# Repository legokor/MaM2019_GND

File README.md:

# MaM2019-GND

Lábkiosztás:

| ESP32 | LoRa  | Panel |
|-------|-------|-------|
| 5     | NSS   |       |
| 12    |       | Pin8  |
| 14    |       | Pin6  |
| 17    | RESET |       |
| 18    | SCK   |       |
| 19    | MISO  |       |
| 23    | MOSI  |       |
| 25    |       | Pin1  |
| 26    |       | Pin2  |
| 27    |       | Pin4  |
| 32    |       | Pin5  |
| 33    |       | Pin3  |
| 34    | DIO0  |       |
| 35    |       | Pin7  |

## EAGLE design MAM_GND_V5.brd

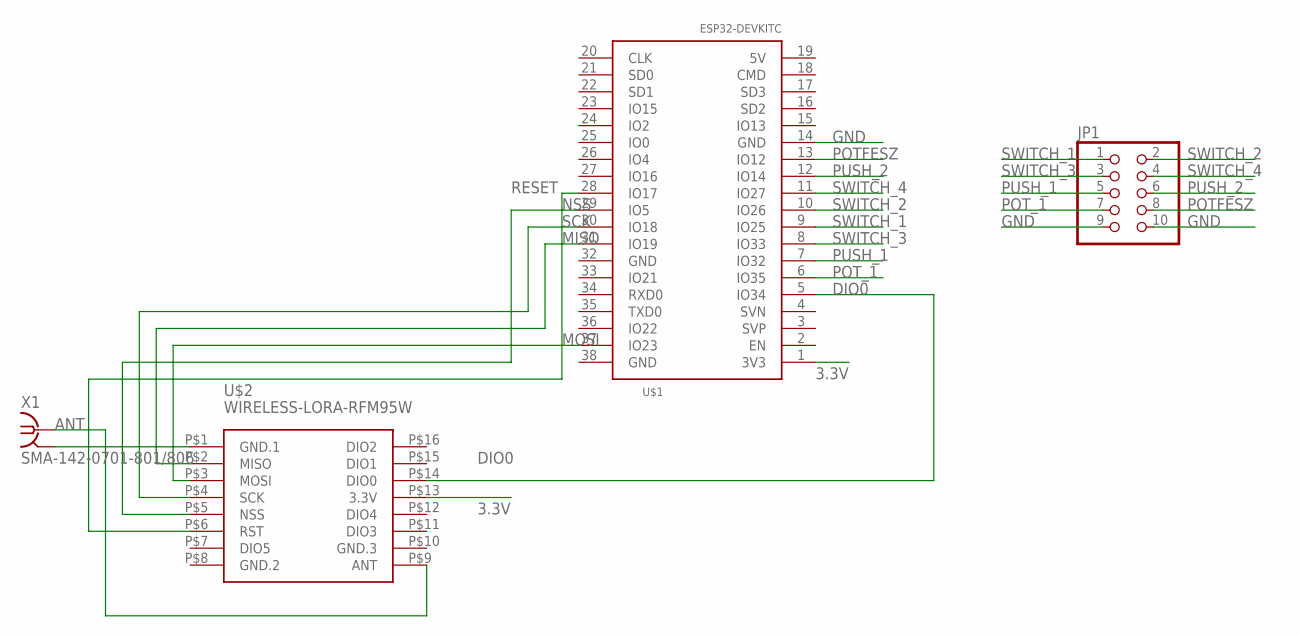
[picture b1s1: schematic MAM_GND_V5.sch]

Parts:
JP1: PINHD-2X5; 2X05
U$1: ESP32DEVKITC; ESP32-DEVKITC
U$2: WIRELESS-LORA-RFM95W; LORA-BREAKOUT
X1: SMA-142-0701-801/806; J502-ND-142-0701-801/806

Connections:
3.3V: U$1.1 (3V3), U$2.P$13 (3.3V)
ANT: U$2.P$9 (ANT), X1.1
DIO0: U$1.5 (IO34), U$2.P$14 (DIO0)
GND: JP1.9, JP1.10, U$1.14 (GND), U$2.P$1 (GND.1), X1.G@1 (2), X1.G@2 (2), X1.G@3 (2), X1.G@4 (2)
GND.2: U$2.P$8 (GND.2)
GND.3: U$2.P$10 (GND.3)
MISO: U$1.31 (IO19), U$2.P$2 (MISO)
MOSI: U$1.37 (IO23), U$2.P$3 (MOSI)
NSS: U$1.29 (IO5), U$2.P$5 (NSS)
POTFESZ: JP1.8, U$1.13 (IO12)
POT_1: JP1.7, U$1.6 (IO35)
PUSH_1: JP1.5, U$1.7 (IO32)
PUSH_2: JP1.6, U$1.12 (IO14)
RESET: U$1.28 (IO17), U$2.P$6 (RST)
SCK: U$1.30 (IO18), U$2.P$4 (SCK)
SWITCH_1: JP1.1, U$1.9 (IO25)
SWITCH_2: JP1.2, U$1.10 (IO26)
SWITCH_3: JP1.3, U$1.8 (IO33)
SWITCH_4: JP1.4, U$1.11 (IO27)

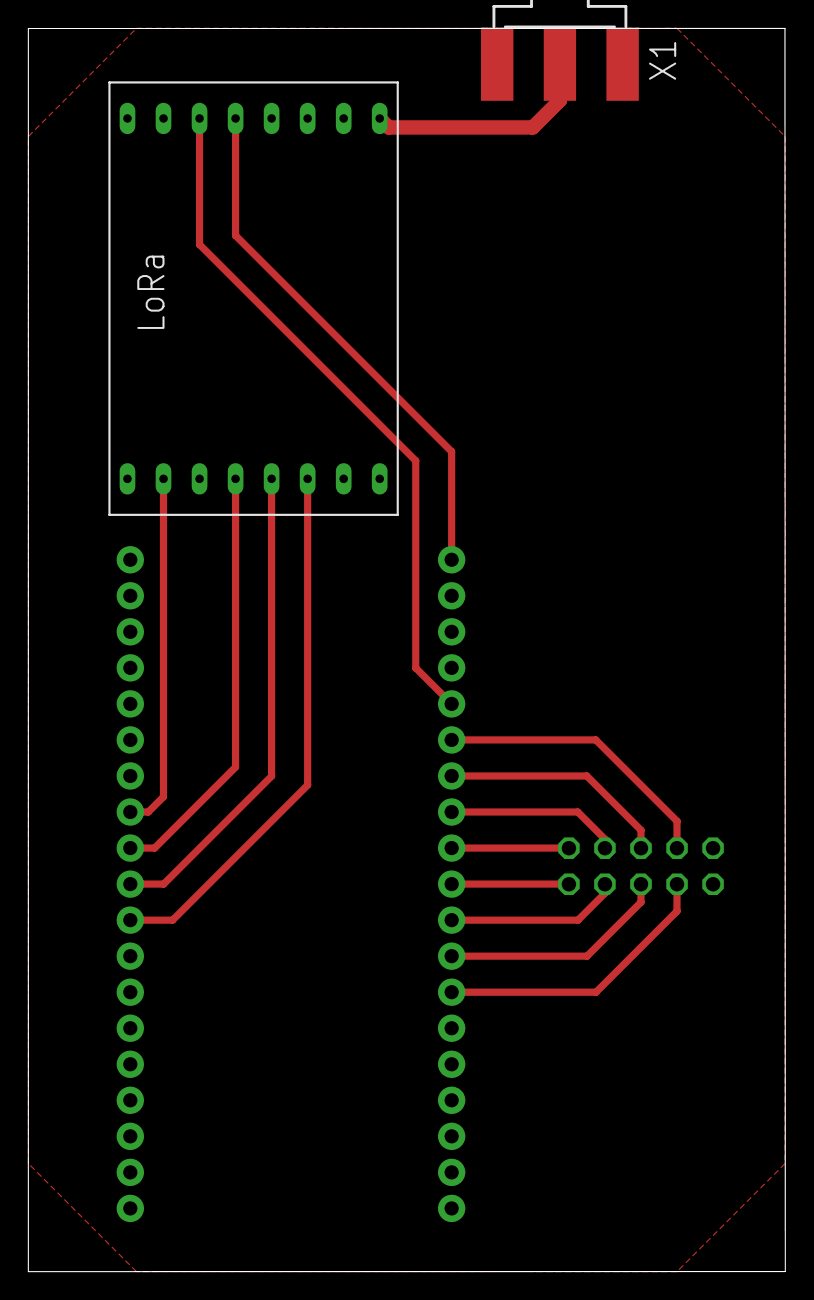
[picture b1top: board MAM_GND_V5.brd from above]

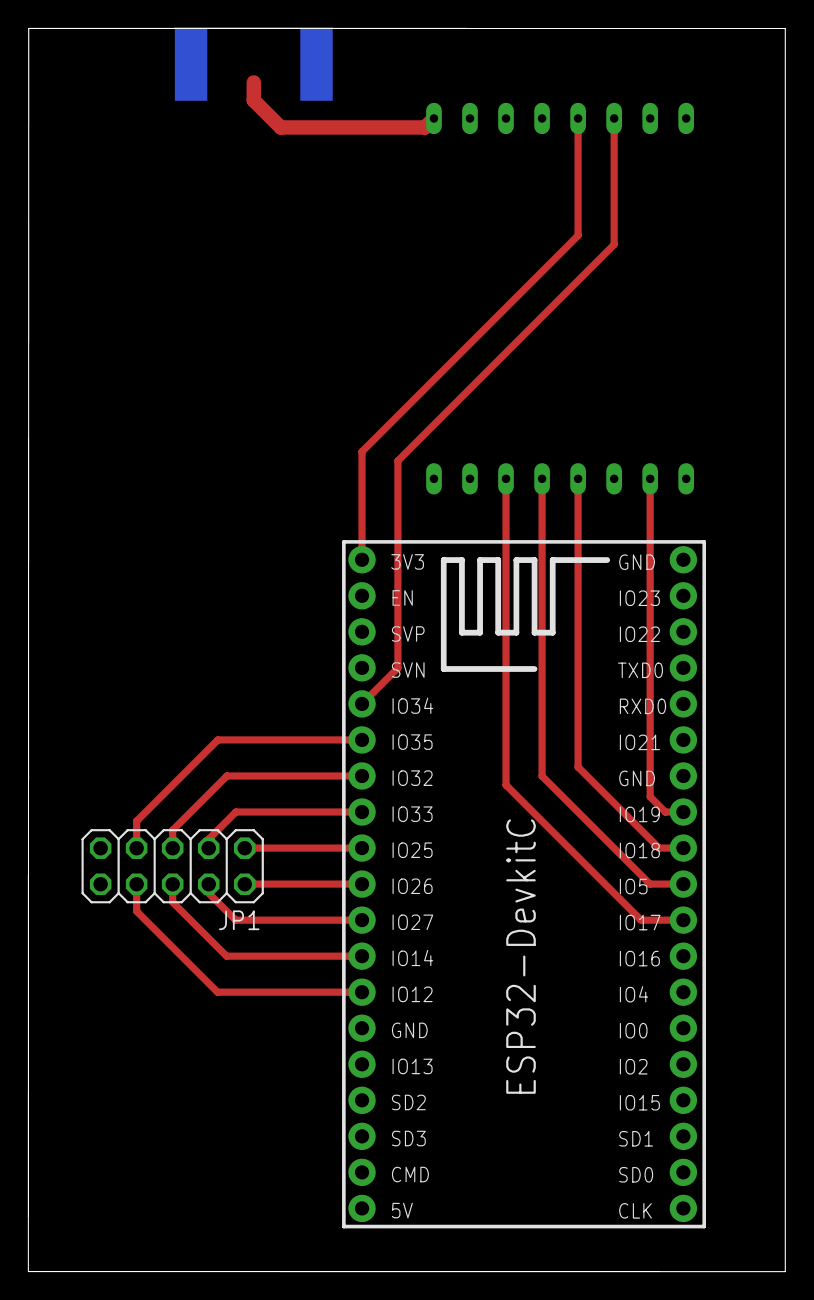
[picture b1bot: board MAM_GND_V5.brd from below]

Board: 2 copper layers, 53.4 x 87.6 mm, 4 parts (2 on the bottom side), 17 nets.

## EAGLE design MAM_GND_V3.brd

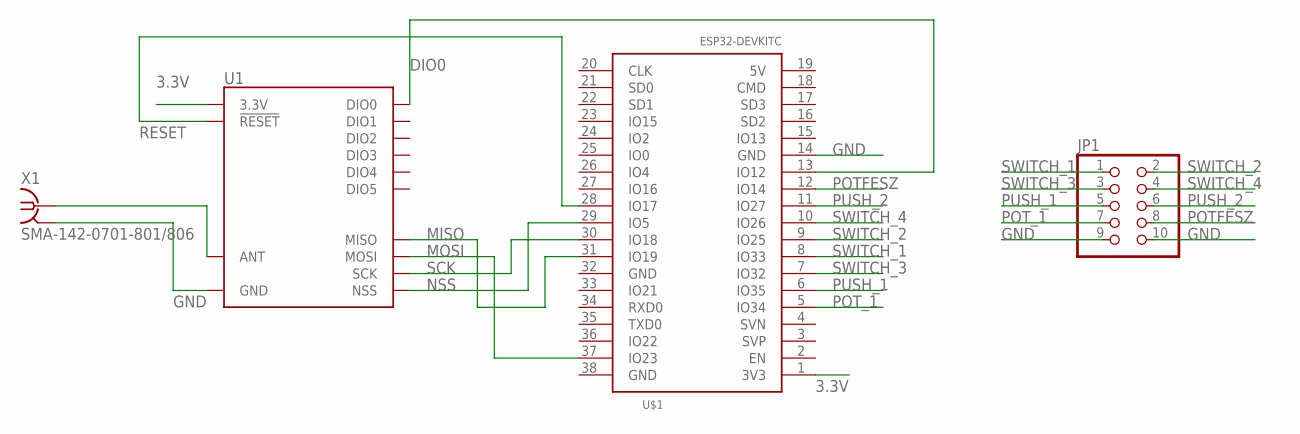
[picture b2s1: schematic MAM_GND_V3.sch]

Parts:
JP1: PINHD-2X5; 2X05
U1: RFM95W; RFM95/96/97/98W
U$1: ESP32DEVKITC; ESP32-DEVKITC
X1: SMA-142-0701-801/806; J502-ND-142-0701-801/806

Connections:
3.3V: U1.3.3V, U$1.1 (3V3)
DIO0: U1.DIO0, U$1.13 (IO12)
GND: JP1.9, JP1.10, U1.GND@1 (GND), U1.GND@2 (GND), U1.GND@3 (GND), U$1.14 (GND), X1.G@1 (2), X1.G@2 (2), X1.G@3 (2), X1.G@4 (2)
MISO: U1.MISO, U$1.31 (IO19)
MOSI: U1.MOSI, U$1.37 (IO23)
unnamed: U1.ANT, X1.1
NSS: U1.NSS, U$1.29 (IO5)
POTFESZ: JP1.8, U$1.12 (IO14)
POT_1: JP1.7, U$1.5 (IO34)
PUSH_1: JP1.5, U$1.6 (IO35)
PUSH_2: JP1.6, U$1.11 (IO27)
RESET: U1.!RESET, U$1.28 (IO17)
SCK: U1.SCK, U$1.30 (IO18)
SWITCH_1: JP1.1, U$1.8 (IO33)
SWITCH_2: JP1.2, U$1.9 (IO25)
SWITCH_3: JP1.3, U$1.7 (IO32)
SWITCH_4: JP1.4, U$1.10 (IO26)

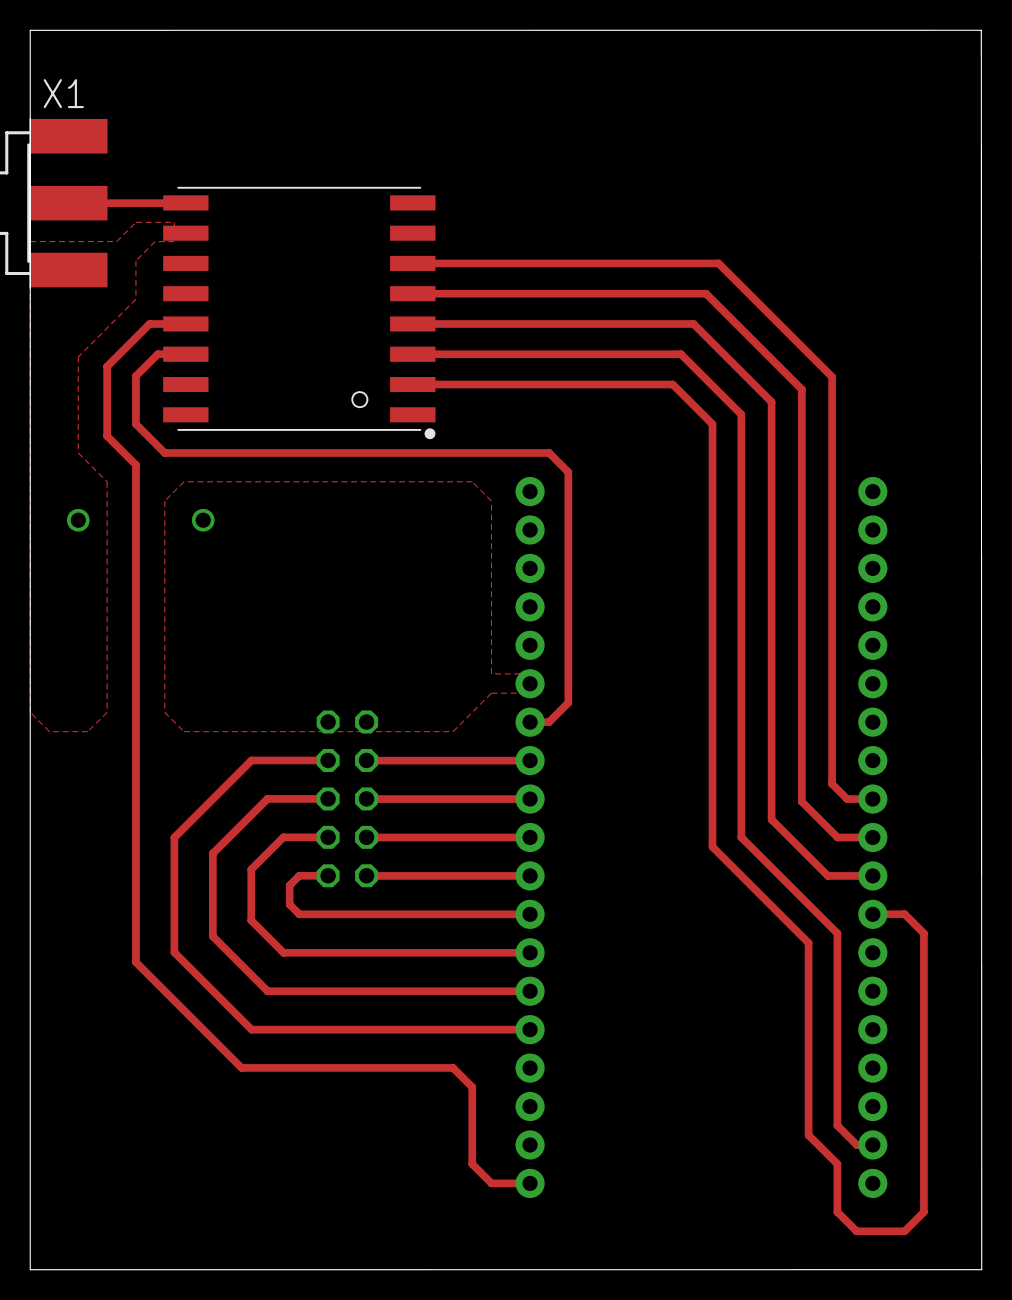
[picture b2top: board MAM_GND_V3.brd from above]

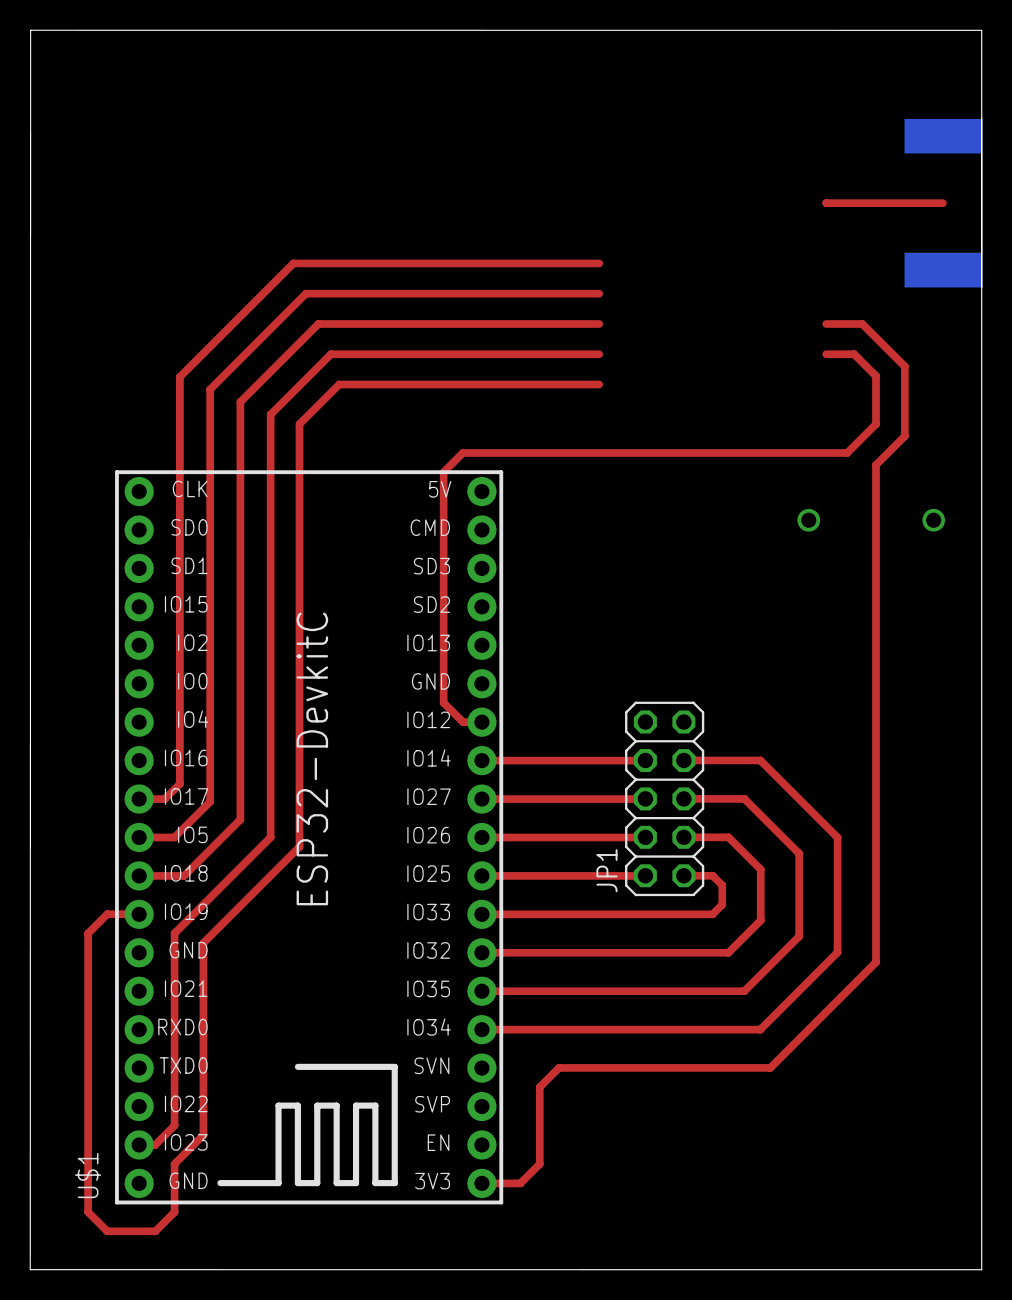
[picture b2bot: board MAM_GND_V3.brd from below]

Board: 2 copper layers, 62.9 x 81.9 mm, 4 parts (2 on the bottom side), 17 nets.

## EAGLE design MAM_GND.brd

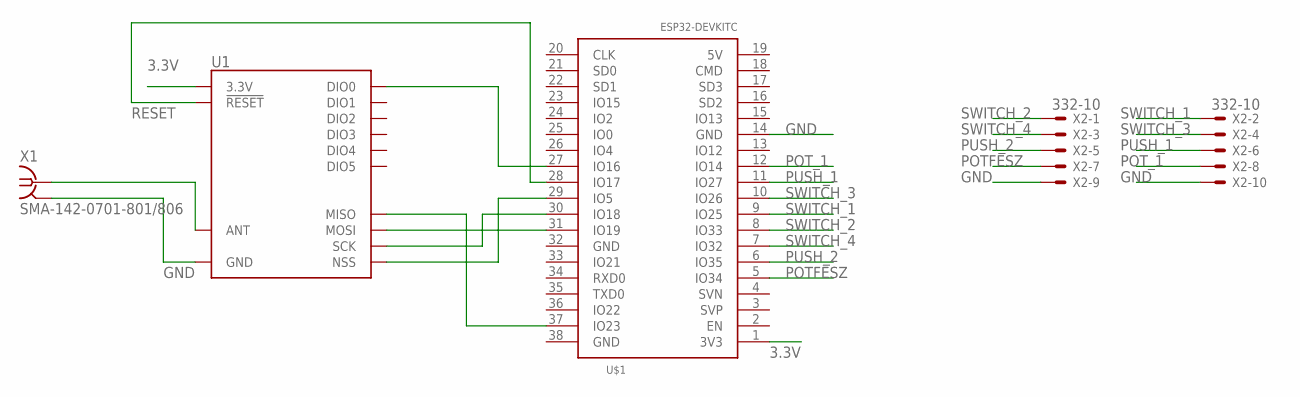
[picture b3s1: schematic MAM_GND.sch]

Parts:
U1: RFM95W; RFM95/96/97/98W
U$1: ESP32DEVKITC; ESP32-DEVKITC
X1: SMA-142-0701-801/806; J502-ND-142-0701-801/806
X2: 332-10

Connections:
3.3V: U1.3.3V, U$1.1 (3V3)
GND: U1.GND@1 (GND), U1.GND@2 (GND), U1.GND@3 (GND), U$1.14 (GND), X1.G@1 (2), X1.G@2 (2), X1.G@3 (2), X1.G@4 (2), X2.9, X2.10
unnamed: U1.MISO, U$1.37 (IO23)
unnamed: U1.MOSI, U$1.31 (IO19)
unnamed: U1.SCK, U$1.30 (IO18)
unnamed: U1.NSS, U$1.29 (IO5)
unnamed: U1.DIO0, U$1.27 (IO16)
unnamed: U1.ANT, X1.1
POTFESZ: U$1.5 (IO34), X2.7
POT_1: U$1.12 (IO14), X2.8
PUSH_1: U$1.11 (IO27), X2.6
PUSH_2: U$1.6 (IO35), X2.5
RESET: U1.!RESET, U$1.28 (IO17)
SWITCH_1: U$1.9 (IO25), X2.2
SWITCH_2: U$1.8 (IO33), X2.1
SWITCH_3: U$1.10 (IO26), X2.4
SWITCH_4: U$1.7 (IO32), X2.3

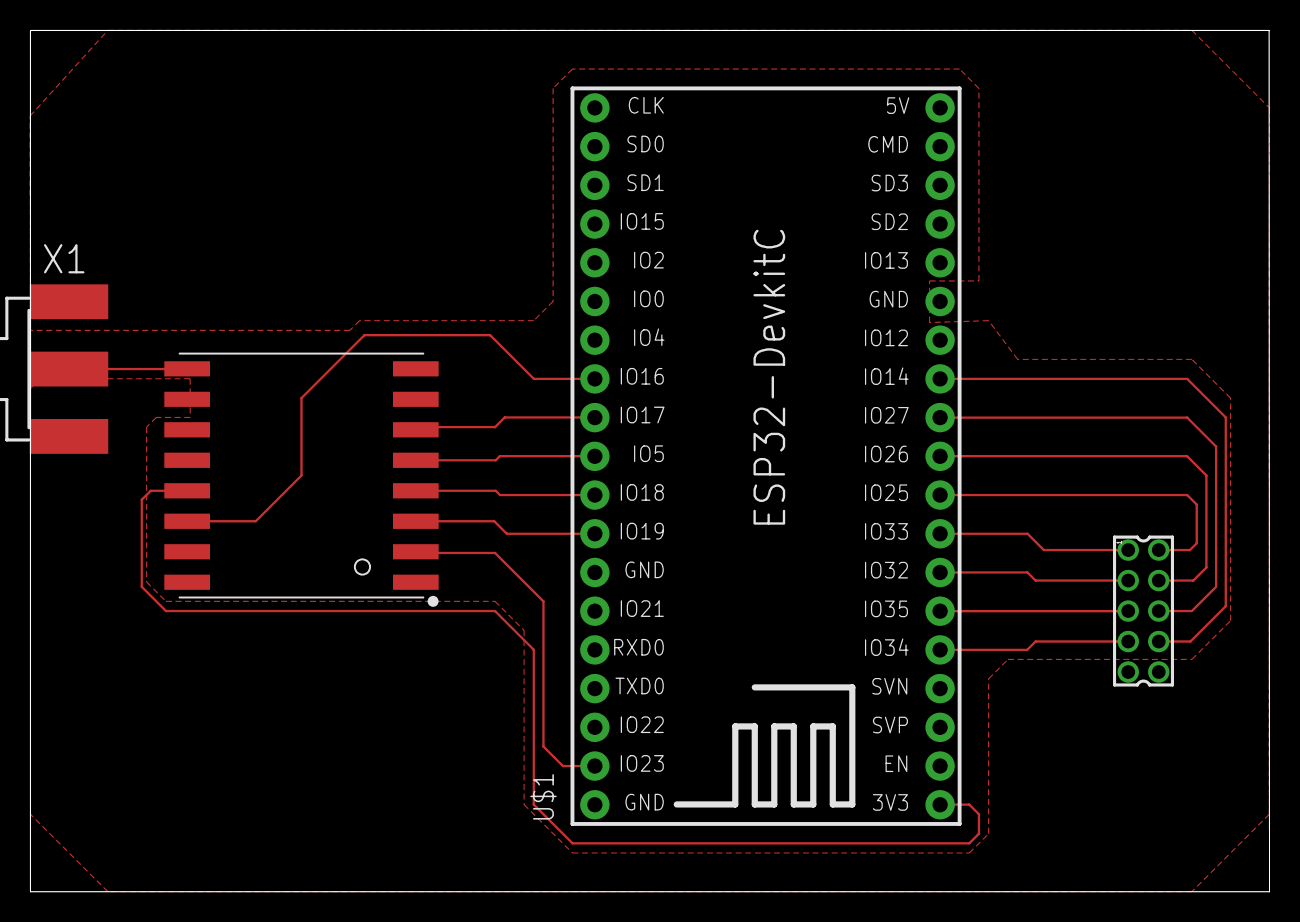
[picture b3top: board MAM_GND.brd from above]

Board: 2 copper layers, 81.3 x 56.5 mm, 4 parts (0 on the bottom side), 17 nets.

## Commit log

2019-07-28 GND nyákterv
    Sajnos, a két földet össze kell kötni egy dróttal, de ezen kívül remélem ez a végleges változat.
2019-07-29 GND nyák
    Sikerült megoldani a föld külön összekötése nélkül :)
2019-07-29 table for pins
2019-07-30 added pdf to print
2019-09-13 Lora modul kapcsolási rajza
    Ezen a könyvtáron belül az RFM95W-t használtam a GND tervezésénél.
2020-03-08 Legújabb GND panel terv
2020-03-10 updated lora pads

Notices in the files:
parts and their libraries:
SparkFun-RF: Licensing: Creative Commons ShareAlike 4.0 International - https://creativecommons.org/licenses/by-sa/4.0
